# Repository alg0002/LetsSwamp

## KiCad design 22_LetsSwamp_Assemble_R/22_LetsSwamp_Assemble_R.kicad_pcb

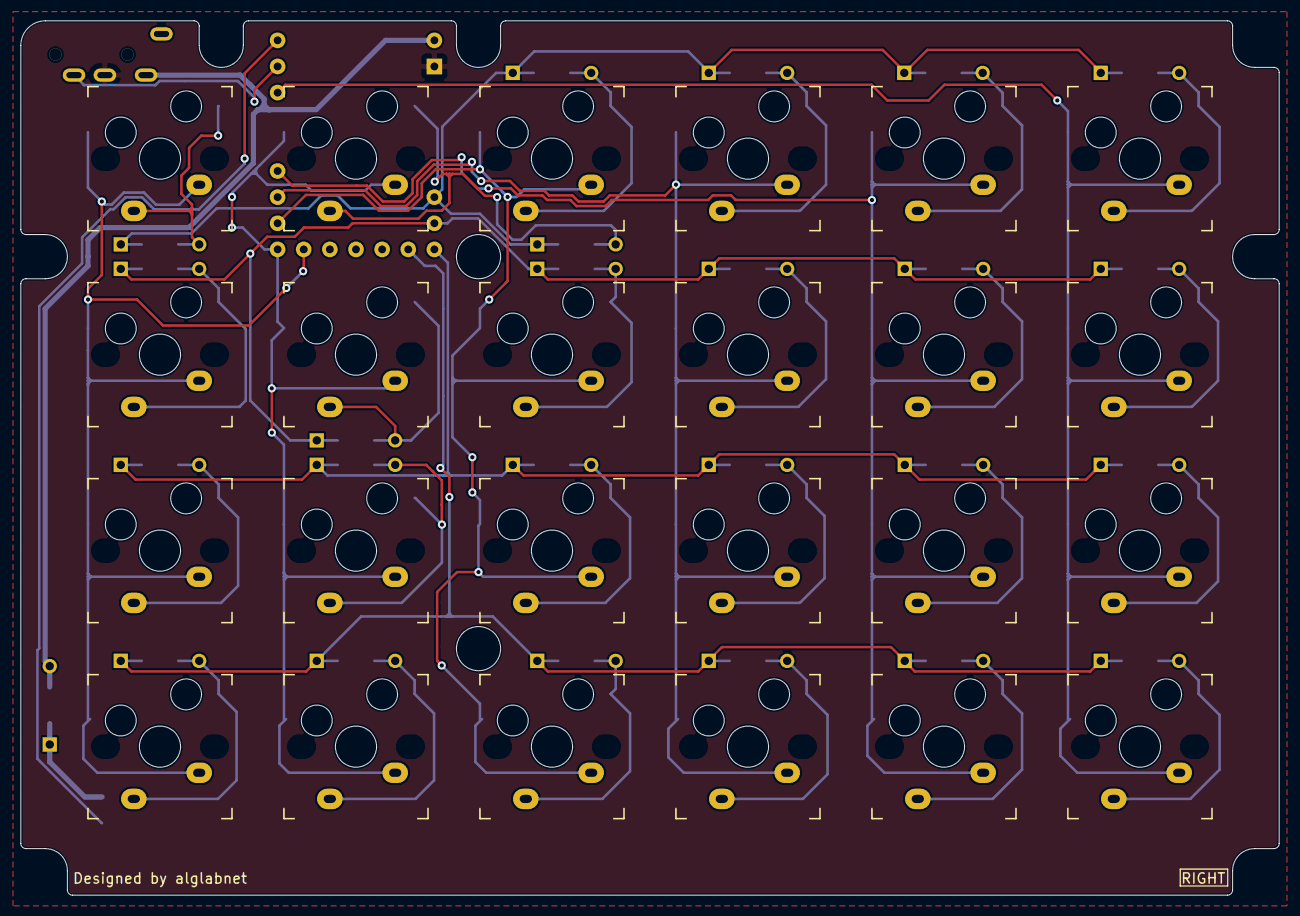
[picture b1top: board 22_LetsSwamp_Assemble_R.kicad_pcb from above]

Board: 2 copper layers, 122.3 x 85.0 mm, 52 parts (1 on the bottom side), 39 nets.

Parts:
D26, D27, D28, D29, D30, D31, D32, D33, D34, D35, D36, D37, D38, D39, D40, D41, D42, D43, D44, D45, D46, D47, D48, D49, D50: D; Diode_TH_SMD
J1: MJ-4PP-9; TRRS_MJ-4PP-9
J2: Conn_01x03; LED_Tape
SW26, SW27, SW28, SW29, SW30, SW31, SW32, SW33, SW34, SW35, SW36, SW37, SW38, SW39, SW40, SW41, SW42, SW43, SW44, SW45, SW46, SW47, SW48, SW49: SW_Push; CherryMX_HotswapAndSolder_1u
U1: Waveshare_RP2040-Zero; Waveshare_RP2040-Zero_Reverse_OmitPins

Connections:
COL0: SW26.1, SW27.1, SW28.1, SW29.1, U1.14
COL1: SW30.1, SW31.1, SW32.1, SW33.1, U1.15
COL2: SW34.1, SW35.1, SW36.1, SW37.1, U1.16
COL3: SW38.1, SW39.1, SW40.1, SW41.1, U1.17
COL4: SW42.1, SW43.1, SW44.1, SW45.1, U1.18
COL5: SW46.1, SW47.1, SW48.1, SW49.1, U1.21
DATA: J1.B, U1.22
GND: J1.C, J2.1, U1.2
LED: J2.2, U1.23
unnamed: D26.2, SW26.2
unnamed: D27.2, SW27.2
unnamed: D28.2, SW28.2
unnamed: D29.2, SW29.2
unnamed: D30.2, SW30.2
unnamed: D31.2, SW31.2
unnamed: D32.2, SW32.2
unnamed: D33.2, SW33.2
unnamed: D34.2, SW34.2
unnamed: D35.2, SW35.2
unnamed: D36.2, SW36.2
unnamed: D37.2, SW37.2
unnamed: D38.2, SW38.2
unnamed: D39.2, SW39.2
unnamed: D40.2, SW40.2
unnamed: D41.2, SW41.2
unnamed: D42.2, SW42.2
unnamed: D43.2, SW43.2
unnamed: D44.2, SW44.2
unnamed: D45.2, SW45.2
unnamed: D46.2, SW46.2
unnamed: D47.2, SW47.2
unnamed: D48.2, SW48.2
unnamed: D49.2, SW49.2
unnamed: D50.1, J2.3
ROW0: D26.1, D30.1, D34.1, D38.1, D42.1, D46.1, U1.7
ROW1: D27.1, D31.1, D35.1, D39.1, D43.1, D47.1, U1.8
ROW2: D28.1, D32.1, D36.1, D40.1, D44.1, D48.1, U1.9
ROW3: D29.1, D33.1, D37.1, D41.1, D45.1, D49.1, U1.10
VCC: D50.2, J1.D, U1.1
